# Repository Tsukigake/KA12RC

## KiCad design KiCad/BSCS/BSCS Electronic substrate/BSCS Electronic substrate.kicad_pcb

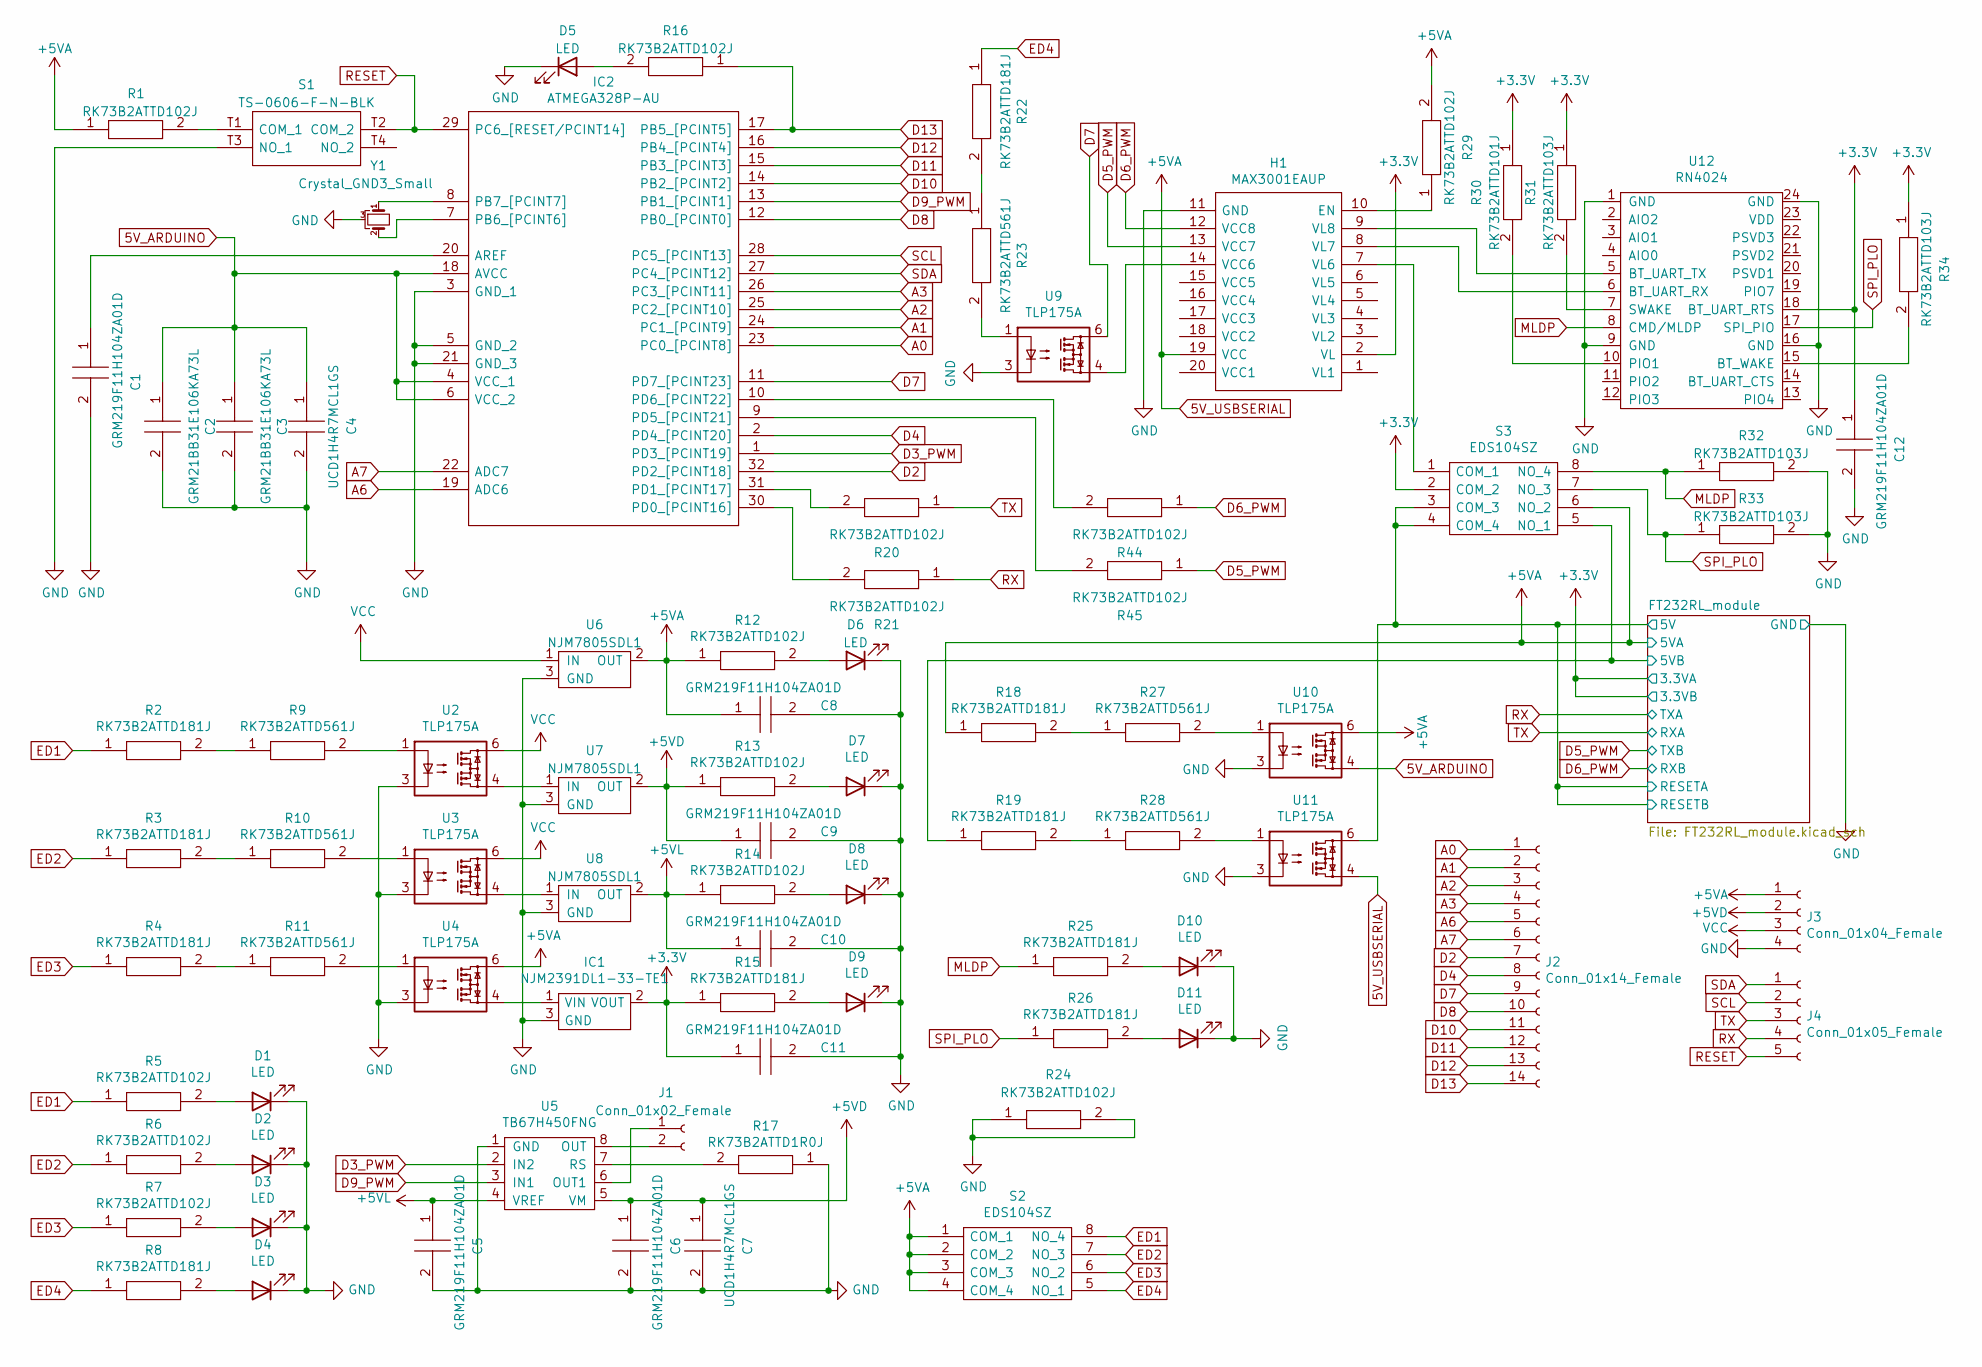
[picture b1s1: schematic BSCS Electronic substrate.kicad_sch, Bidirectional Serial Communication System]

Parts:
C1, C5, C6, C8, C9, C10, C11, C12: GRM219F11H104ZA01D; CAPC2012X95N; Manufacturer_Part_Number GRM219F11H104ZA01D
C2, C3: GRM21BB31E106KA73L; CAPC2012X140N; Manufacturer_Part_Number GRM21BB31E106KA73L
C4, C7: UCD1H4R7MCL1GS; CAPAE430X610N; Manufacturer_Part_Number UCD1H4R7MCL1GS
D1, D2, D3, D4, D5, D6, D7, D8, D9, D10, D11: LED; OSXX0603C1E
H1: MAX3001EAUP; SOP65P640X110-20N; Manufacturer_Part_Number MAX3001EAUP
IC1: NJM2391DL1-33-TE1; TO-252-3-L1; Manufacturer_Part_Number NJM2391DL1-33-TE1
IC2: ATMEGA328P-AU; QFP80P900X900X120-32N; Manufacturer_Part_Number ATMEGA328P-AU
J1: Conn_01x02_Female; PinHeader_1x02_P2.54mm_Vertical
J2: Conn_01x14_Female; PinHeader_1x14_P2.54mm_Vertical
J3: Conn_01x04_Female; PinHeader_1x04_P2.54mm_Vertical
J4: Conn_01x05_Female; PinHeader_1x05_P2.54mm_Vertical
R1, R5, R6, R7, R12, R13, R14, R16, R20, R21, R24, R29, R44, R45: RK73B2ATTD102J; RESC2012X60N; Manufacturer_Part_Number RK73B2ATTD102J
R2, R3, R4, R8, R15, R18, R19, R22, R25, R26: RK73B2ATTD181J; RESC2012X60N; Manufacturer_Part_Number RK73B2ATTD181J
R9, R10, R11, R23, R27, R28: RK73B2ATTD561J; RESC2012X60N; Manufacturer_Part_Number RK73B2ATTD561J
R17: RK73B2ATTD1R0J; RESC2012X60N; Manufacturer_Part_Number RK73B2ATTD1R0J
R30: RK73B2ATTD101J; RESC2012X60N; Manufacturer_Part_Number RK73B2ATTD101J
R31, R32, R33, R34: RK73B2ATTD103J; RESC2012X60N; Manufacturer_Part_Number RK73B2ATTD103J
S1: TS-0606-F-N-BLK; TS0606FNBLK; Manufacturer_Part_Number TS-0606-F-N-BLK
S2, S3: EDS104SZ; KHS42E; Manufacturer_Part_Number EDS104SZ
U2, U3, U4, U9, U10, U11: TLP175A; MFSOP6-4_4.4x3.6mm_P1.27mm
U5: TB67H450FNG; NE555DR
U6, U7, U8: NJM7805SDL1; TO-252-3-L1
U12: RN4024
Y1: Crystal_GND3_Small; CSTCE16M0V53R0

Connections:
5V_ARDUINO: C2.1, C3.1, C4.1, IC2.4 (VCC_1), IC2.6 (VCC_2), IC2.18 (AVCC), U10.4
5V_USBSERIAL: C8.1, H1.19 (VCC), J3.1, R1.1, R12.1, R18.1, R29.2, S2.1 (COM_1), S2.2 (COM_2), S2.3 (COM_3), S2.4 (COM_4), S3.6 (NO_2), U4.6, U6.2 (OUT), U10.6, U11.4; also elsewhere on the board
+3V3: C11.1, C12.1, H1.2 (VL), IC1.2 (VOUT), R15.1, R30.1, R31.1, R34.1, S3.2 (COM_2), U12.18 (BT_UART_RTS); also elsewhere on the board
+5VD: C6.1, C7.1, C9.1, J3.2, R13.1, U5.5 (VM), U7.2 (OUT)
+5VL: C5.1, C10.1, R14.1, U5.4 (VREF), U8.2 (OUT)
/FT232RL_module/5V: S3.3 (COM_3), S3.4 (COM_4), U11.6; also elsewhere on the board
/FT232RL_module/5VB: R19.1, S3.5 (NO_1); also elsewhere on the board
A0: IC2.23 (PC0_[PCINT8]), J2.1
A1: IC2.24 (PC1_[PCINT9]), J2.2
A2: IC2.25 (PC2_[PCINT10]), J2.3
A3: IC2.26 (PC3_[PCINT11]), J2.4
A6: IC2.19 (ADC6), J2.5
A7: IC2.22 (ADC7), J2.6
D2: IC2.32 (PD2_[PCINT18]), J2.7
D3_PWM: IC2.1 (PD3_[PCINT19]), U5.2 (IN2)
D4: IC2.2 (PD4_[PCINT20]), J2.8
D5_PWM: H1.13 (VCC7), R45.1; also elsewhere on the board
D6_PWM: H1.12 (VCC8), R44.1; also elsewhere on the board
D7: IC2.11 (PD7_[PCINT23]), J2.9, U9.6
D8: IC2.12 (PB0_[PCINT0]), J2.10
D9_PWM: IC2.13 (PB1_[PCINT1]), U5.3 (IN1)
D10: IC2.14 (PB2_[PCINT2]), J2.11
D11: IC2.15 (PB3_[PCINT3]), J2.12
D12: IC2.16 (PB4_[PCINT4]), J2.13
D13: IC2.17 (PB5_[PCINT5]), J2.14, R16.1
ED1: R2.1, R5.1, S2.8 (NO_4)
ED2: R3.1, R6.1, S2.7 (NO_3)
ED3: R4.1, R7.1, S2.6 (NO_2)
ED4: R8.1, R22.1, S2.5 (NO_1)
GND: C1.2, C2.2, C3.2, C4.2, C5.2, C6.2, C7.2, C8.2, C9.2, C10.2, C11.2, C12.2, D1.1 (K), D2.1 (K), D3.1 (K), D4.1 (K), D5.1 (K), D6.1 (K), D7.1 (K), D8.1 (K), D9.1 (K), D10.1 (K), D11.1 (K), H1.11 (GND), IC1.3 (GND), IC2.3 (GND_1), IC2.5 (GND_2), IC2.21 (GND_3), J3.4, R17.1, R24.1, R24.2, R32.2, R33.2, S1.T3 (NO_1), U2.3, U3.3, U4.3, U5.1 (GND), U6.3 (GND), U7.3 (GND), U8.3 (GND), U9.3, U10.3, U11.3, U12.1 (GND), U12.9 (GND), U12.16 (GND), U12.24 (GND), Y1.3; also elsewhere on the board
MLDP: R25.1, R32.1, S3.8 (NO_4), U12.8 (CMD/MLDP)
unnamed: C1.1, IC2.20 (AREF)
unnamed: D1.2 (A), R5.2
unnamed: D2.2 (A), R6.2
unnamed: D3.2 (A), R7.2
unnamed: D4.2 (A), R8.2
unnamed: D5.2 (A), R16.2
unnamed: D6.2 (A), R12.2
unnamed: D7.2 (A), R13.2
unnamed: D8.2 (A), R14.2
unnamed: D9.2 (A), R15.2
unnamed: D10.2 (A), R25.2
unnamed: D11.2 (A), R26.2
unnamed: H1.7 (VL6), S3.1 (COM_1)
unnamed: H1.8 (VL7), U12.6 (BT_UART_RX)
unnamed: H1.9 (VL8), U12.5 (BT_UART_TX)
unnamed: H1.10 (EN), R29.1
unnamed: H1.14 (VCC6), U9.4
unnamed: IC1.1 (VIN), U4.4
unnamed: IC2.7 (PB6_[PCINT6]), Y1.2
unnamed: IC2.8 (PB7_[PCINT7]), Y1.1
unnamed: IC2.9 (PD5_[PCINT21]), R45.2
unnamed: IC2.10 (PD6_[PCINT22]), R44.2
unnamed: IC2.30 (PD0_[PCINT16]), R21.2
unnamed: IC2.31 (PD1_[PCINT17]), R20.2
unnamed: J1.1, U5.6 (OUT1)
unnamed: J1.2, U5.8 (OUT)
unnamed: R1.2, S1.T1 (COM_1)
unnamed: R2.2, R9.1
unnamed: R9.2, U2.1
unnamed: R3.2, R10.1
unnamed: R10.2, U3.1
unnamed: R4.2, R11.1
unnamed: R11.2, U4.1
unnamed: R17.2, U5.7 (RS)
unnamed: R18.2, R27.1
unnamed: R19.2, R28.1
unnamed: R22.2, R23.1
unnamed: R23.2, U9.1
unnamed: R27.2, U10.1
unnamed: R28.2, U11.1
unnamed: R30.2, U12.10 (PIO1)
unnamed: R31.2, U12.7 (SWAKE)
unnamed: R34.2, U12.15 (BT_WAKE)
unnamed: U2.4, U7.1 (IN)
unnamed: U3.4, U8.1 (IN)
RESET: IC2.29 (PC6_[RESET/PCINT14]), J4.5, S1.T2 (COM_2)
RX: J4.4, R21.1; also elsewhere on the board
SCL: IC2.28 (PC5_[PCINT13]), J4.2
SDA: IC2.27 (PC4_[PCINT12]), J4.1
SPI_PLO: R26.1, R33.1, S3.7 (NO_3), U12.17 (SPI_PIO)
TX: J4.3, R20.1; also elsewhere on the board
VCC: J3.3, U2.6, U3.6, U6.1 (IN)

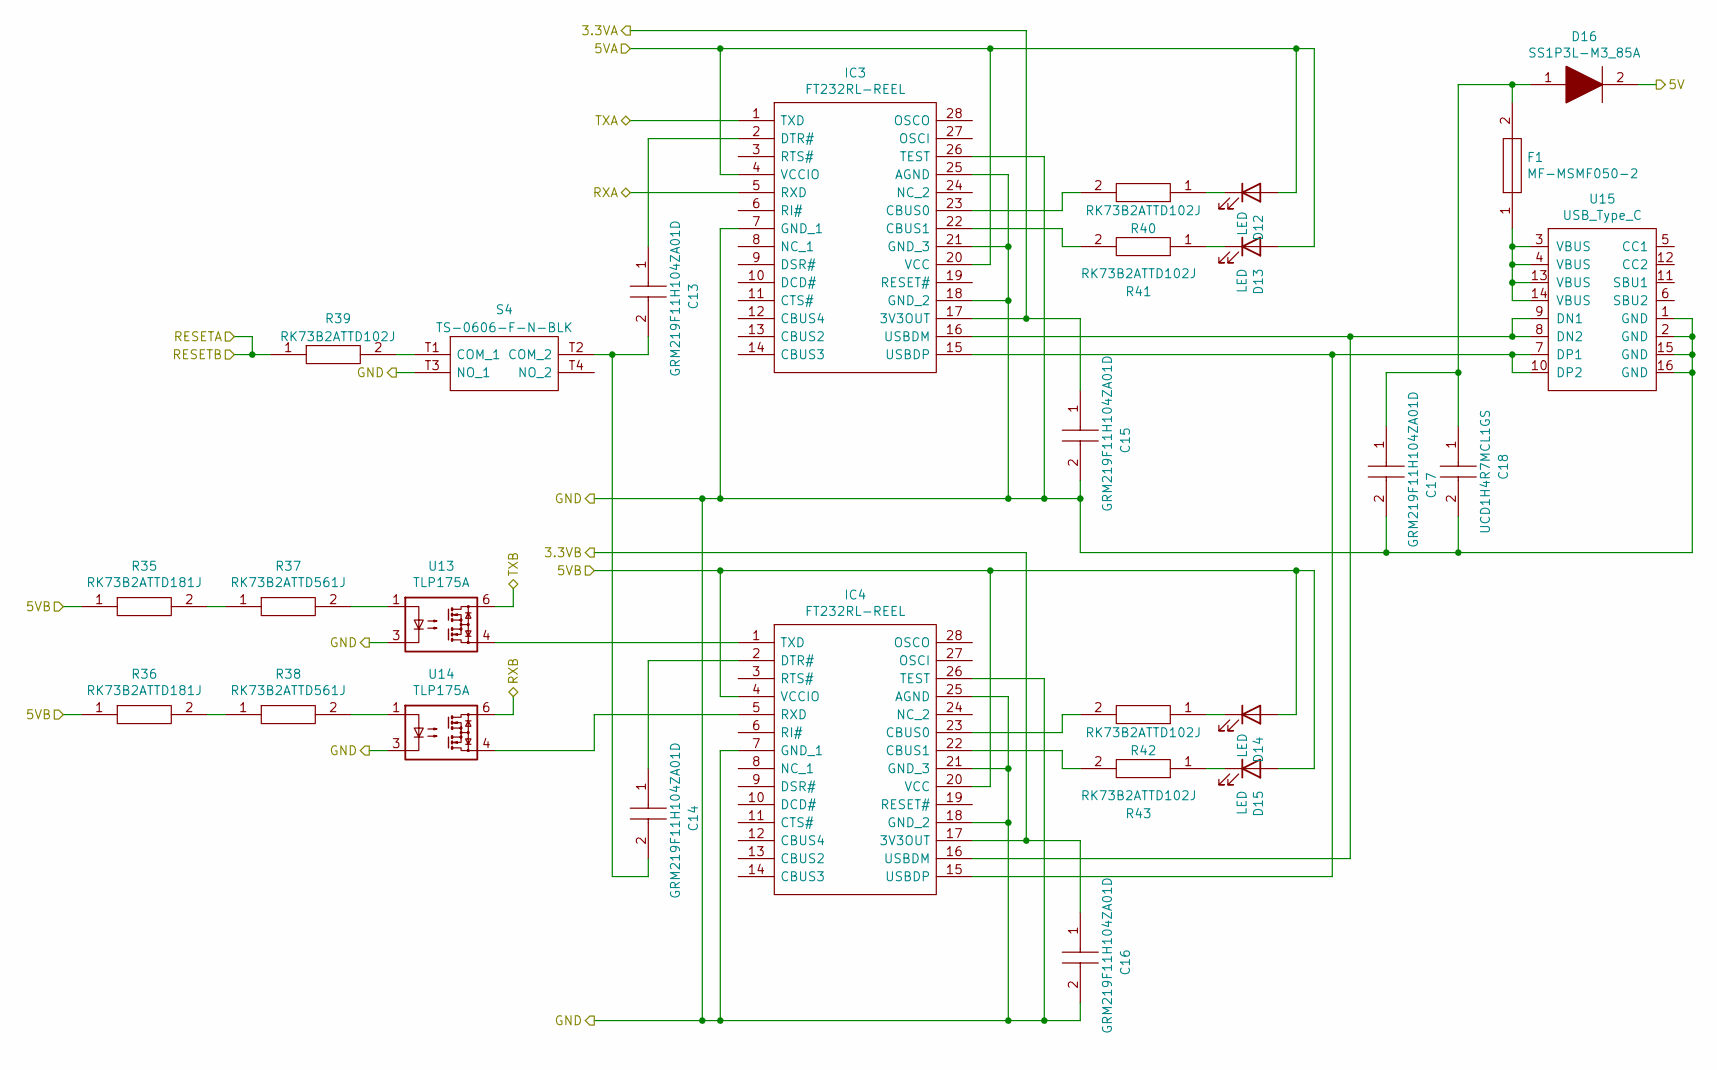
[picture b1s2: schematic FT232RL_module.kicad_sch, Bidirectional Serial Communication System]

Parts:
C13, C14, C15, C16, C17: GRM219F11H104ZA01D; CAPC2012X95N; Manufacturer_Part_Number GRM219F11H104ZA01D
C18: UCD1H4R7MCL1GS; CAPAE430X610N; Manufacturer_Part_Number UCD1H4R7MCL1GS
D12, D13, D14, D15: LED; OSXX0603C1E
D16: SS1P3L-M3_85A; SMP; Manufacturer_Part_Number SS1P3L-M3/85A
F1: MF-MSMF050-2; FUSC4632X85N; Manufacturer_Part_Number MF-MSMF050-2
IC3, IC4: FT232RL-REEL; SOP65P778X200-28N; Manufacturer_Part_Number FT232RL-REEL
R35, R36: RK73B2ATTD181J; RESC2012X60N; Manufacturer_Part_Number RK73B2ATTD181J
R37, R38: RK73B2ATTD561J; RESC2012X60N; Manufacturer_Part_Number RK73B2ATTD561J
R39, R40, R41, R42, R43: RK73B2ATTD102J; RESC2012X60N; Manufacturer_Part_Number RK73B2ATTD102J
S4: TS-0606-F-N-BLK; TS0606FNBLK; Manufacturer_Part_Number TS-0606-F-N-BLK
U13, U14: TLP175A; MFSOP6-4_4.4x3.6mm_P1.27mm
U15: USB_Type_C

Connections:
5V_USBSERIAL: D12.2 (A), D13.2 (A), IC3.4 (VCCIO), IC3.20 (VCC); also elsewhere on the board
+3V3: C15.1, C16.1, IC3.17 (3V3OUT), IC4.17 (3V3OUT); also elsewhere on the board
/FT232RL_module/5V: D16.2, R39.1; also elsewhere on the board
/FT232RL_module/5VB: D14.2 (A), D15.2 (A), IC4.4 (VCCIO), IC4.20 (VCC), R35.1, R36.1; also elsewhere on the board
D5_PWM: U13.6; also elsewhere on the board
D6_PWM: U14.6; also elsewhere on the board
GND: C15.2, C16.2, C17.2, C18.2, IC3.7 (GND_1), IC3.18 (GND_2), IC3.21 (GND_3), IC3.25 (AGND), IC3.26 (TEST), IC4.7 (GND_1), IC4.18 (GND_2), IC4.21 (GND_3), IC4.25 (AGND), IC4.26 (TEST), S4.T3 (NO_1), U13.3, U14.3, U15.1 (GND), U15.2 (GND), U15.15 (GND), U15.16 (GND); also elsewhere on the board
unnamed: C13.1, IC3.2 (DTR#)
unnamed: C13.2, C14.2, S4.T2 (COM_2)
unnamed: C14.1, IC4.2 (DTR#)
unnamed: C17.1, C18.1, D16.1, F1.2
unnamed: D12.1 (K), R40.1
unnamed: D13.1 (K), R41.1
unnamed: D14.1 (K), R42.1
unnamed: D15.1 (K), R43.1
unnamed: F1.1, U15.3 (VBUS), U15.4 (VBUS), U15.13 (VBUS), U15.14 (VBUS)
unnamed: IC3.15 (USBDP), IC4.15 (USBDP), U15.7 (DP1), U15.10 (DP2)
unnamed: IC3.16 (USBDM), IC4.16 (USBDM), U15.8 (DN2), U15.9 (DN1)
unnamed: IC3.22 (CBUS1), R41.2
unnamed: IC3.23 (CBUS0), R40.2
unnamed: IC4.1 (TXD), U13.4
unnamed: IC4.5 (RXD), U14.4
unnamed: IC4.22 (CBUS1), R43.2
unnamed: IC4.23 (CBUS0), R42.2
unnamed: R35.2, R37.1
unnamed: R36.2, R38.1
unnamed: R37.2, U13.1
unnamed: R38.2, U14.1
unnamed: R39.2, S4.T1 (COM_1)
RX: IC3.1 (TXD); also elsewhere on the board
TX: IC3.5 (RXD); also elsewhere on the board

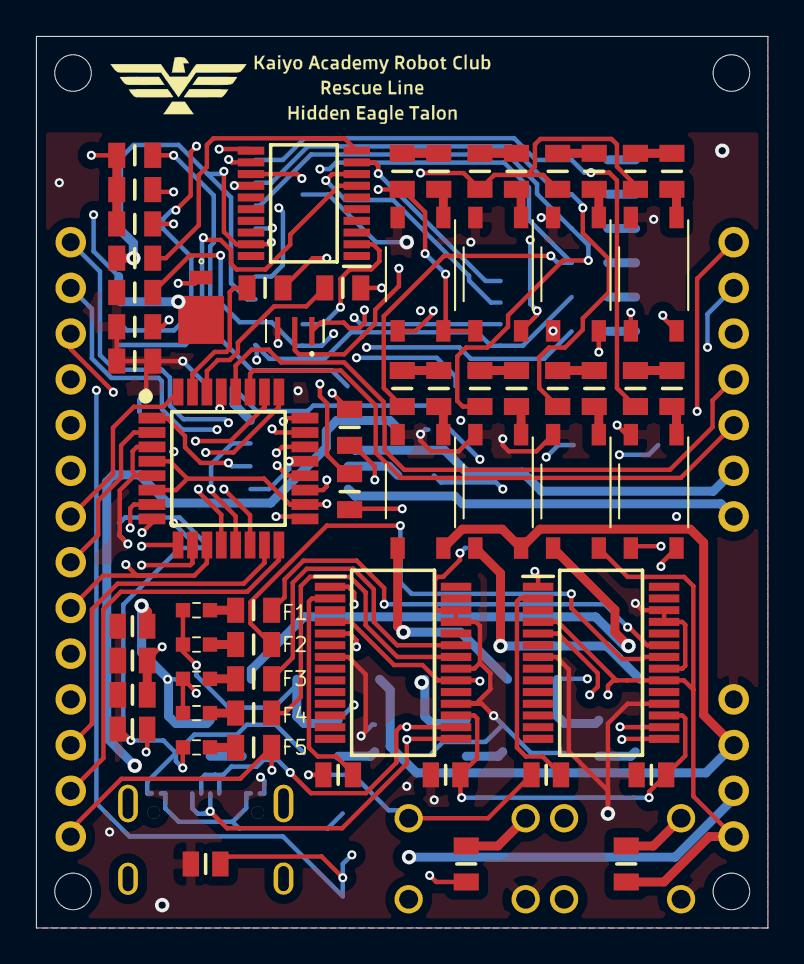
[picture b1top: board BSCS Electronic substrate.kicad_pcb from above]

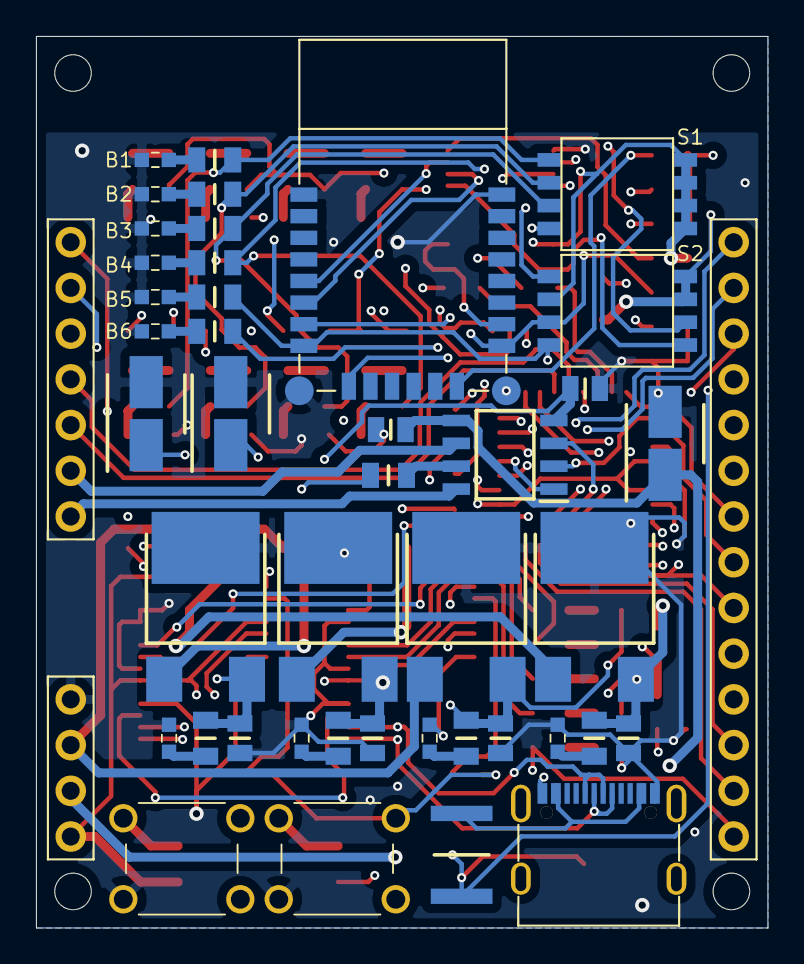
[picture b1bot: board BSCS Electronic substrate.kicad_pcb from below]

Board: 4 copper layers, 40.6 x 49.5 mm, 108 parts (46 on the bottom side), 105 nets.

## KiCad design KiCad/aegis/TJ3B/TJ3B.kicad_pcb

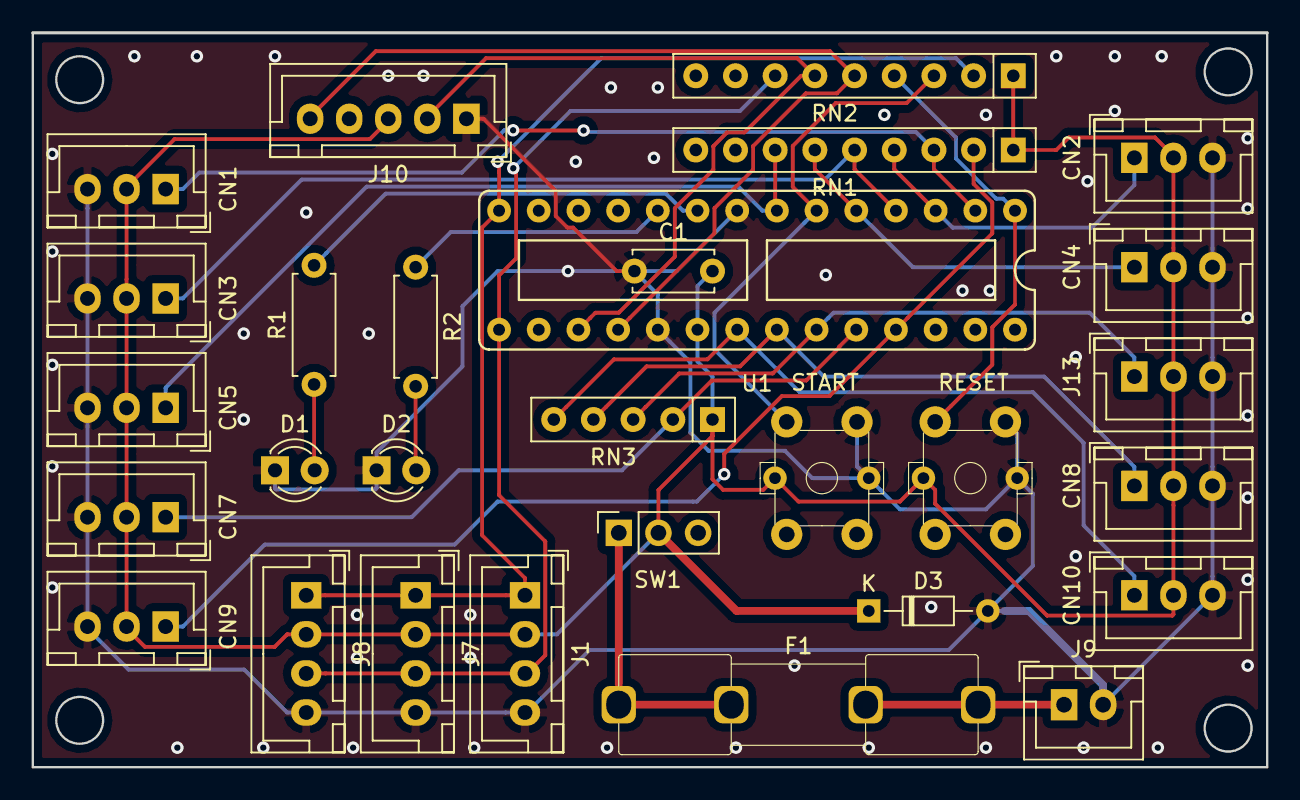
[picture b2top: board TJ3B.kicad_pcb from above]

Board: 2 copper layers, 79.0 x 47.0 mm, 29 parts (0 on the bottom side), 24 nets.

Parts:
C1: 0.1u; C_Disc_D5.0mm_W2.5mm_P5.00mm
CN1, CN2, CN3, CN4, CN5, CN7, CN8, CN9, CN10: Conn_01x03_Female; JST_XH_B03B-XH-A_1x03_P2.50mm_Vertical
D1, D2: LED; LED_D3.0mm
D3: D; D_DO-34_SOD68_P7.62mm_Horizontal
F1: Fuse; fuse
J1, J7, J8: Conn_01x04_Female; JST_XH_B04B-XH-A_1x04_P2.50mm_Vertical
J9: Conn_01x02_Female; JST_XH_B02B-XH-A_1x02_P2.50mm_Vertical
J10: Conn_01x05_Female; JST_XH_B05B-XH-A_1x05_P2.50mm_Vertical
J13: Conn_01x03_Female; JST_XH_B03B-XH-A_1x03_P2.50mm_Vertical
R1, R2: 330; R_Axial_DIN0207_L6.3mm_D2.5mm_P7.62mm_Horizontal
RESET: LS601-CU
RN1: R_100k; R_Array_SIP9
RN2: R_10k; R_Array_SIP9
RN3: R_100k; R_Array_SIP5
START: LS601-CU
SW1: SW_DIP_x01; PinSocket_1x03_P2.54mm_Vertical
U1: PIC18F2620; 2227-28-03

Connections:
+5V: C1.2, CN1.2, CN2.2, CN3.2, CN4.2, CN5.2, CN7.2, CN8.2, CN9.2, CN10.2, D3.1, J1.2, J7.2, J8.2, J10.3, J13.2, RESET.5, RN1.1, RN2.1, RN3.1, START.5, SW1.2, U1.20
AD1: CN1.1, RN1.3, U1.2
AD2: CN2.1, RN1.4, U1.3
AD3: CN3.1, RN1.5, U1.4
AD4: CN4.1, RN1.6, U1.5
AD5: CN5.1, RN1.7, U1.7
AD6: J13.1, RN3.3, U1.23
AD7: CN7.1, RN3.2, U1.24
AD8: CN8.1, RN3.4, U1.22
AD9: CN9.1, RN1.2, U1.25
AD10: CN10.1, RN3.5, U1.21
GND: C1.1, CN1.3, CN2.3, CN3.3, CN4.3, CN5.3, CN7.3, CN8.3, CN9.3, CN10.3, D1.1, D2.1, D3.2, J1.4, J7.4, J8.4, J9.2, J10.1, J13.3, RESET.1, RESET.6, START.1, START.6, U1.8, U1.19
MCLR: RESET.3, RN2.4, U1.1
MON_LED: R2.1, U1.10
unnamed: D1.2, R1.1
unnamed: D2.2, R2.2
unnamed: F1.1, SW1.1
unnamed: F1.2, J9.1
PWM_LED: R1.2, U1.9
RA4: RN2.3, START.3, U1.6
RX: J10.5, RN2.5, U1.18
SCL: J1.1, J7.1, J8.1, RN2.2, U1.14
SDA: J1.3, J7.3, J8.3, RN2.7, U1.15
TX: J10.2, RN2.6, U1.17

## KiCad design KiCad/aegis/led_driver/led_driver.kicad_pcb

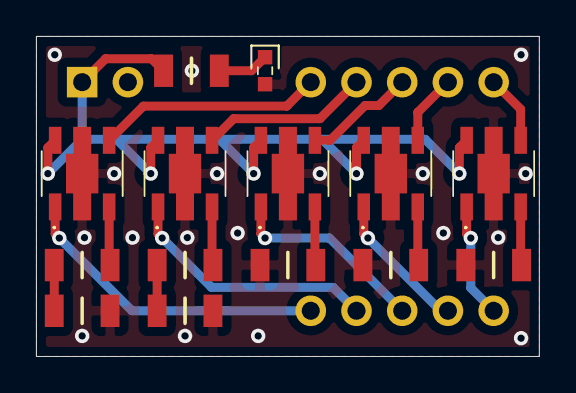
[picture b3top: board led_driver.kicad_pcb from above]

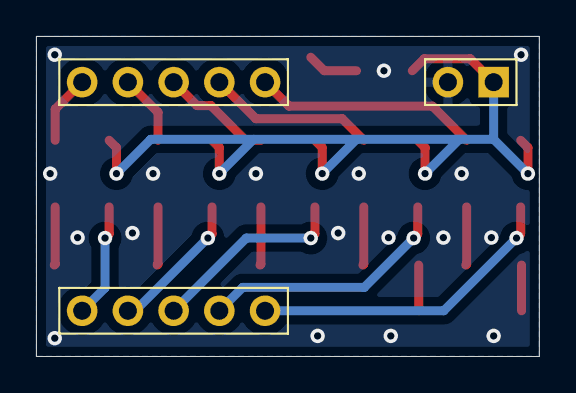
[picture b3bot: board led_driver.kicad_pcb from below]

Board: 2 copper layers, 27.9 x 17.8 mm, 17 parts (3 on the bottom side), 20 nets.

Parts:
J1: Conn_01x02_Male; PinHeader_1x02_P2.54mm_Vertical
J2, J3: Conn_01x05_Male; PinHeader_1x05_P2.54mm_Vertical
J5, J6, J7, J10, J11: NJW4616U2
LED1: OSXX0603C1E
R1, R2, R3, R4, R5, R6, R7: RK73B2BTTD1R0J; RESC3216X80N
R8: RK73B2BTTD221J; RESC3216X70N

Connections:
unnamed: J1.1, J5.6, J6.6, J7.6, J10.6, J11.6, R8.1
unnamed: J1.2, J5.2, J5.5, J5.7, J6.2, J6.5, J6.7, J7.2, J7.5, J7.7, J10.2, J10.5, J10.7, J11.2, J11.5, J11.7, LED1.2, R1.2, R2.2, R3.2, R6.2, R7.2
unnamed: J2.1, J5.1
unnamed: J2.2, J6.1
unnamed: J2.3, J7.1
unnamed: J3.1, J5.4
unnamed: J3.2, J6.4
unnamed: J3.3, J7.4
unnamed: J5.3, R1.1
unnamed: J6.3, R2.1
unnamed: J7.3, R3.1
unnamed: J2.4, J10.1
unnamed: J10.3, R4.1
unnamed: J3.4, J10.4
unnamed: J2.5, J11.1
unnamed: J11.3, R5.1
unnamed: J3.5, J11.4
unnamed: LED1.1, R8.2
unnamed: R4.2, R6.1
unnamed: R5.2, R7.1

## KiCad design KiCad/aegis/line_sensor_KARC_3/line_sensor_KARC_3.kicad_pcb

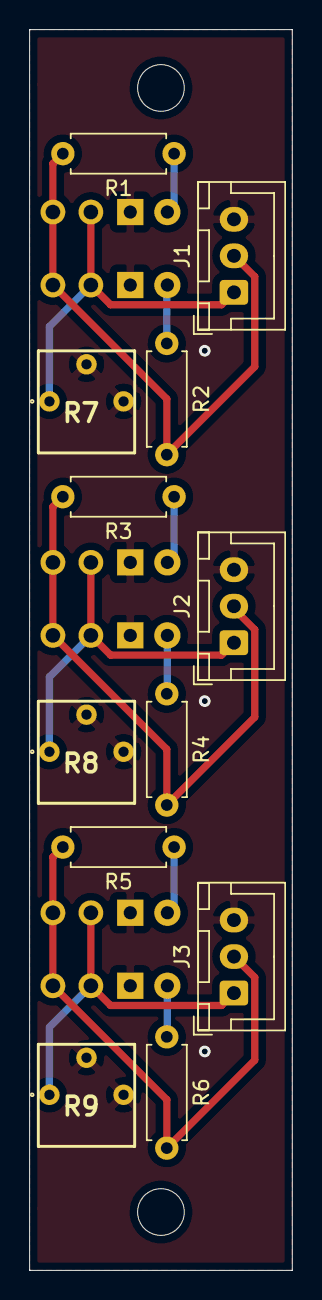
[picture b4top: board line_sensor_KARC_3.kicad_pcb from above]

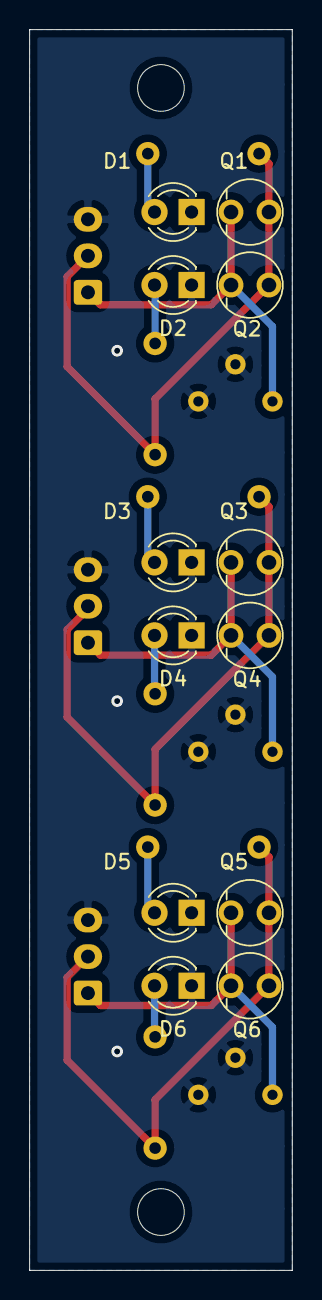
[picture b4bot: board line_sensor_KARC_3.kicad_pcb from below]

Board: 2 copper layers, 18.0 x 85.0 mm, 24 parts (12 on the bottom side), 13 nets.

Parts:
D1, D2, D3, D4, D5, D6: LED; LED_D3.0mm_Clear
J1, J2, J3: Conn_01x03_Male; JST_XH_B3B-XH-A_1x03_P2.50mm_Vertical
Q1, Q2, Q3, Q4, Q5, Q6: Q_Photo_NPN; NJL7502L
R1, R2, R3, R4, R5, R6: R; R_Axial_DIN0207_L6.3mm_D2.5mm_P7.62mm_Horizontal
R7, R8, R9: 3362P-1-203LF; 3362P_1

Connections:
unnamed: D1.1, D2.1, D3.1, D4.1, D5.1, D6.1, J1.3, J2.3, J3.3, R7.2, R7.3, R8.2, R8.3, R9.2, R9.3
unnamed: D1.2, R1.1
unnamed: D2.2, R2.1
unnamed: D3.2, R3.1
unnamed: D4.2, R4.1
unnamed: D5.2, R5.1
unnamed: D6.2, R6.1
unnamed: J1.1, Q1.2, Q2.2, R7.1
unnamed: J1.2, Q1.1, Q2.1, R1.2, R2.2
unnamed: J2.1, Q3.2, Q4.2, R8.1
unnamed: J2.2, Q3.1, Q4.1, R3.2, R4.2
unnamed: J3.1, Q5.2, Q6.2, R9.1
unnamed: J3.2, Q5.1, Q6.1, R5.2, R6.2

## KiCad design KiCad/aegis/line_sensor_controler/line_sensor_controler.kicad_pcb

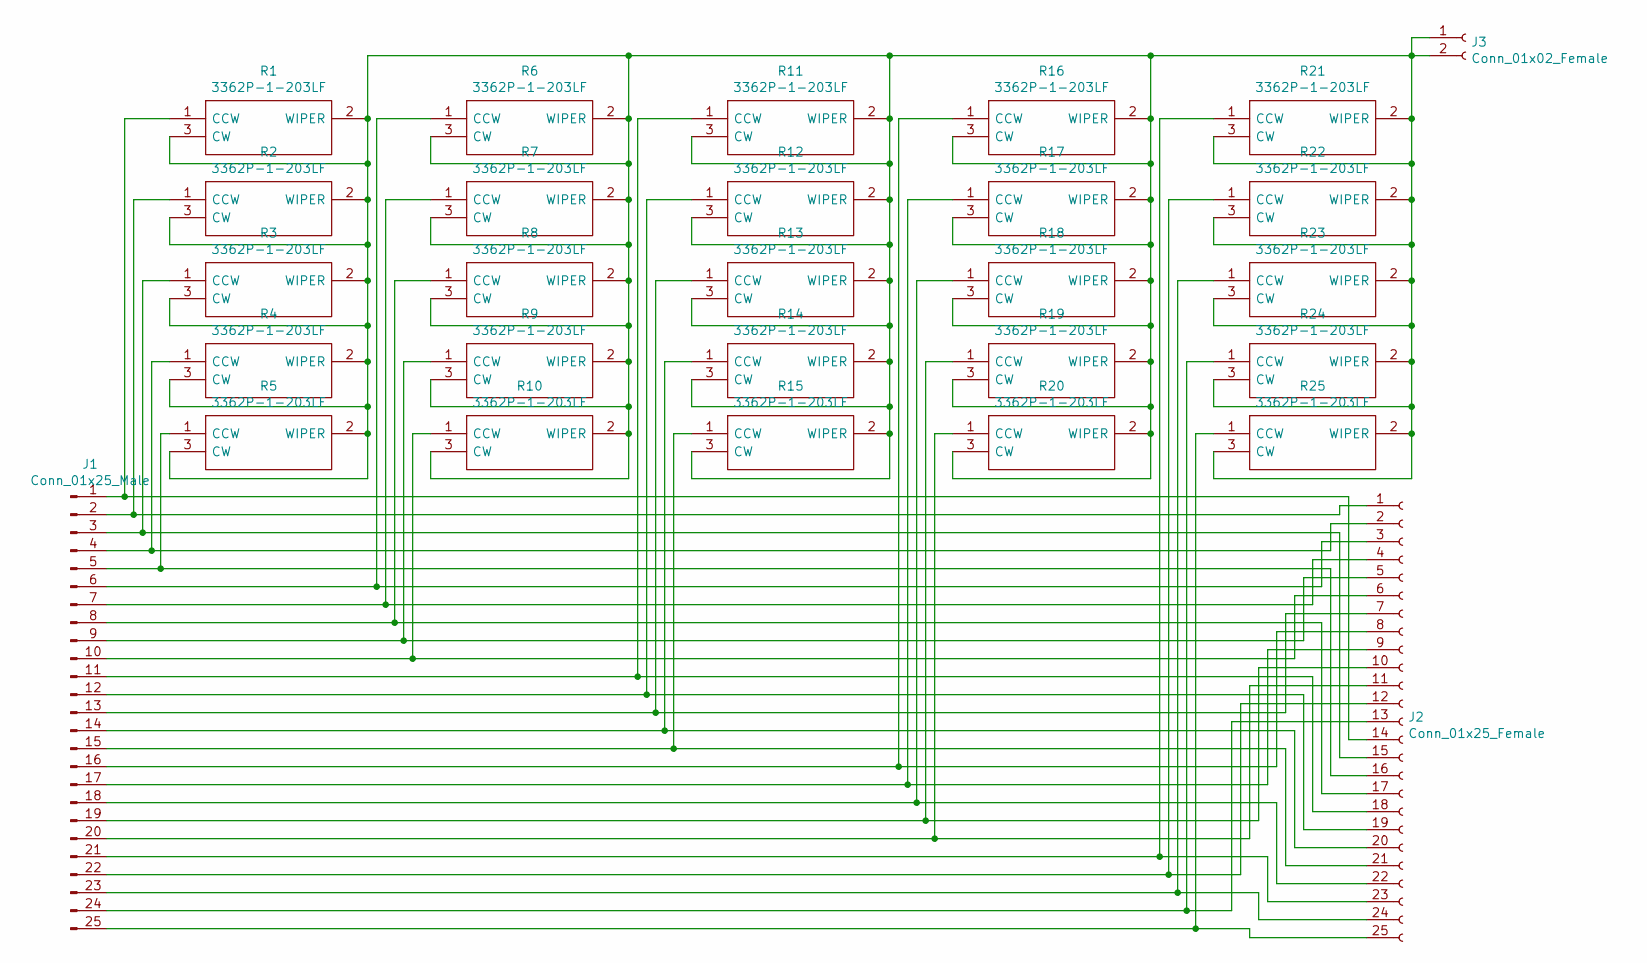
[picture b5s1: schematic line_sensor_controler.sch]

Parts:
J1: Conn_01x25_Male; PinSocket_1x25_P2.54mm_Vertical
J2: Conn_01x25_Female; PinSocket_1x25_P2.54mm_Vertical
J3: Conn_01x02_Female; PinSocket_1x02_P2.54mm_Vertical
R1, R2, R3, R4, R5, R6, R7, R8, R9, R10, R11, R12, R13, R14, R15, R16, R17, R18, R19, R20, R21, R22, R23, R24, R25: 3362P-1-203LF; 3362P_1; Mouser Part Number 652-3362P-1-203LF

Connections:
unnamed: J1.1, J2.14, R1.1 (CCW)
unnamed: J1.2, J2.1, R2.1 (CCW)
unnamed: J1.3, J2.15, R3.1 (CCW)
unnamed: J1.4, J2.2, R4.1 (CCW)
unnamed: J1.5, J2.16, R5.1 (CCW)
unnamed: J1.6, J2.3, R6.1 (CCW)
unnamed: J1.7, J2.4, R7.1 (CCW)
unnamed: J1.8, J2.17, R8.1 (CCW)
unnamed: J1.9, J2.5, R9.1 (CCW)
unnamed: J1.10, J2.6, R10.1 (CCW)
unnamed: J1.11, J2.18, R11.1 (CCW)
unnamed: J1.12, J2.19, R12.1 (CCW)
unnamed: J1.13, J2.7, R13.1 (CCW)
unnamed: J1.14, J2.20, R14.1 (CCW)
unnamed: J1.15, J2.21, R15.1 (CCW)
unnamed: J1.16, J2.8, R16.1 (CCW)
unnamed: J1.17, J2.9, R17.1 (CCW)
unnamed: J1.18, J2.22, R18.1 (CCW)
unnamed: J1.19, J2.10, R19.1 (CCW)
unnamed: J1.20, J2.11, R20.1 (CCW)
unnamed: J1.21, J2.23, R21.1 (CCW)
unnamed: J1.22, J2.12, R22.1 (CCW)
unnamed: J1.23, J2.24, R23.1 (CCW)
unnamed: J1.24, J2.13, R24.1 (CCW)
unnamed: J1.25, J2.25, R25.1 (CCW)
unnamed: J3.1, J3.2, R1.2 (WIPER), R1.3 (CW), R2.2 (WIPER), R2.3 (CW), R3.2 (WIPER), R3.3 (CW), R4.2 (WIPER), R4.3 (CW), R5.2 (WIPER), R5.3 (CW), R6.2 (WIPER), R6.3 (CW), R7.2 (WIPER), R7.3 (CW), R8.2 (WIPER), R8.3 (CW), R9.2 (WIPER), R9.3 (CW), R10.2 (WIPER), R10.3 (CW), R11.2 (WIPER), R11.3 (CW), R12.2 (WIPER), R12.3 (CW), R13.2 (WIPER), R13.3 (CW), R14.2 (WIPER), R14.3 (CW), R15.2 (WIPER), R15.3 (CW), R16.2 (WIPER), R16.3 (CW), R17.2 (WIPER), R17.3 (CW), R18.2 (WIPER), R18.3 (CW), R19.2 (WIPER), R19.3 (CW), R20.2 (WIPER), R20.3 (CW), R21.2 (WIPER), R21.3 (CW), R22.2 (WIPER), R22.3 (CW), R23.2 (WIPER), R23.3 (CW), R24.2 (WIPER), R24.3 (CW), R25.2 (WIPER), R25.3 (CW)

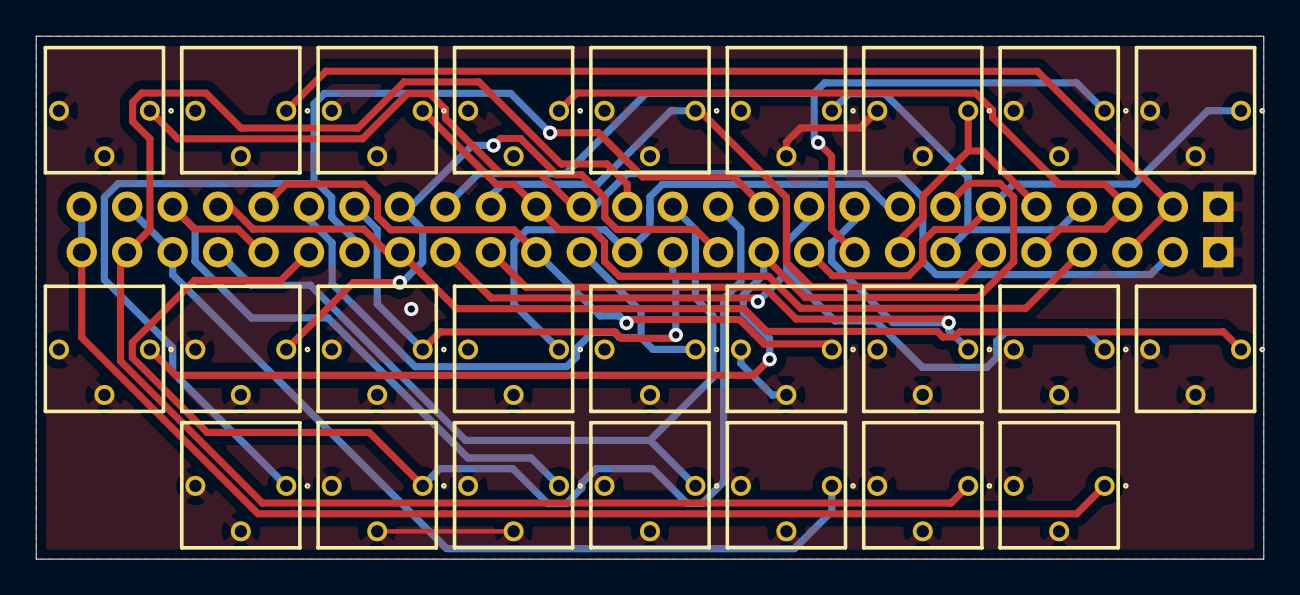
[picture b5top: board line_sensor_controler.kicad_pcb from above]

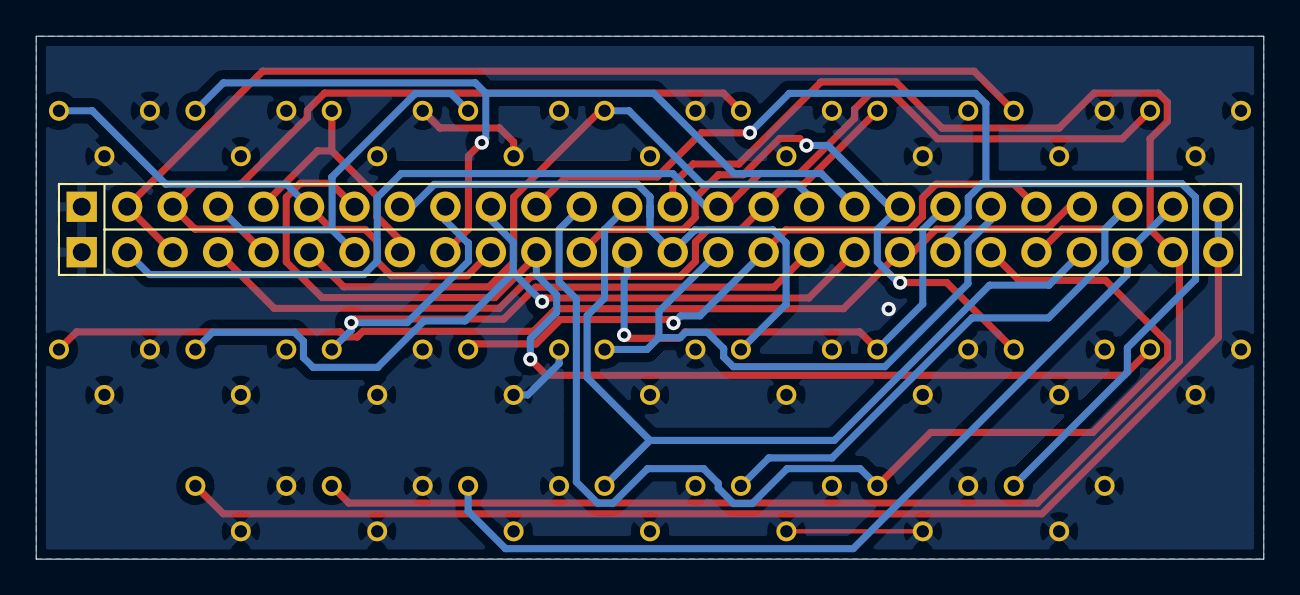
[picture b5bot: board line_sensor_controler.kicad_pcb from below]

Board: 2 copper layers, 68.6 x 29.2 mm, 28 parts (3 on the bottom side), 26 nets.

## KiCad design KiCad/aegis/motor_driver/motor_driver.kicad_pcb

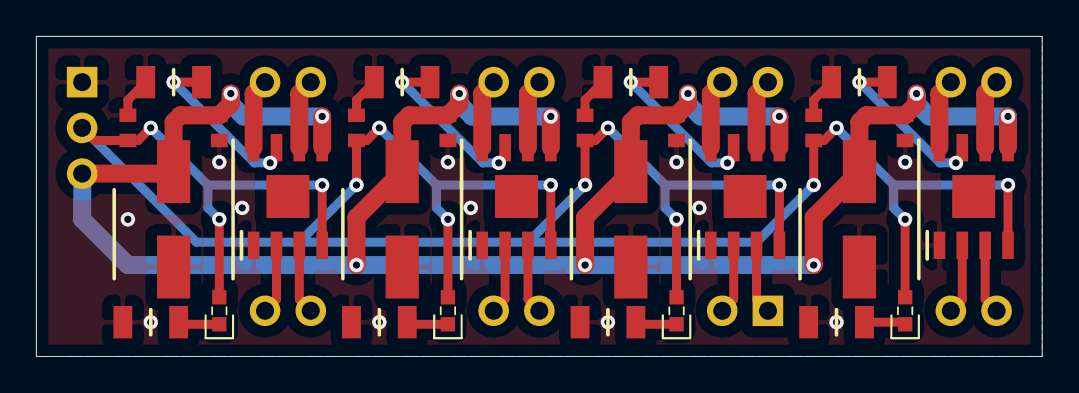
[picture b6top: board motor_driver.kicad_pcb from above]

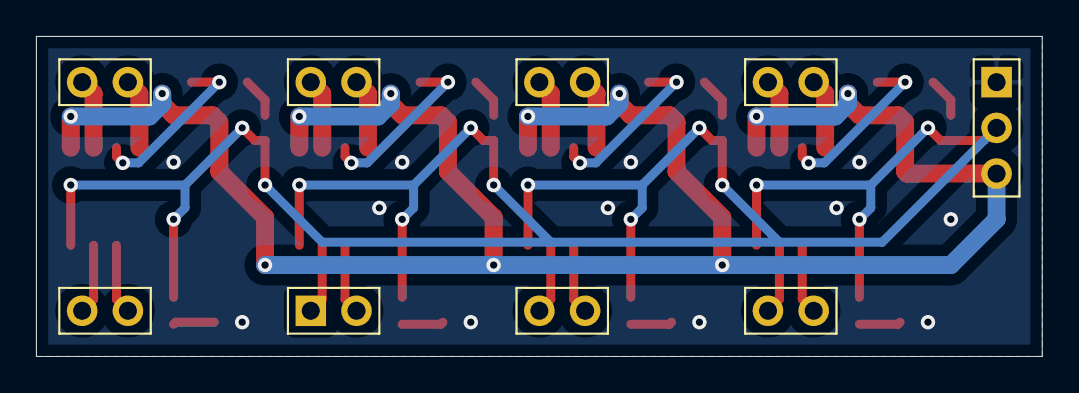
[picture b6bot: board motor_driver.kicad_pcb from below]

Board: 2 copper layers, 55.9 x 17.8 mm, 37 parts (9 on the bottom side), 27 nets.

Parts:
C1, C2, C3, C4, C5, C6, C7, C8: 0.1u; CAPC1608X90N
C9, C10, C11, C12: 47u; CAPAE660X730N
D1, D2, D3, D4: LED; OSXX0603C1E
J1: Conn_01x03_Female; PinHeader_1x03_P2.54mm_Vertical
J2, J3, J4, J5, J6, J7, J8, J9: Conn_01x02_Female; PinHeader_1x02_P2.54mm_Vertical
R1, R2, R3, R4: 110; RESC3216X70N
R5, R6, R7, R8: 1; RESC3216X80N
U3, U4, U5, U6: TB67H450FNG; SOIC127P600X175-9N

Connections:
unnamed: C1.1, C2.1, C3.1, C4.1, D1.2, D2.2, D3.2, D4.2, J1.2, U3.4, U4.4, U5.4, U6.4
unnamed: C1.2, C2.2, C3.2, C4.2, C5.2, C6.2, C7.2, C8.2, C9.2, C10.2, C11.2, C12.2, J1.1, R1.1, R2.1, R3.1, R4.1, R5.1, R6.1, R7.1, R8.1, U3.1, U4.1, U5.1, U6.1
unnamed: C5.1, C6.1, C7.1, C8.1, C9.1, C10.1, C11.1, C12.1, J1.3, U3.5, U4.5, U5.5, U6.5
unnamed: D1.1, R1.2
unnamed: D2.1, R2.2
unnamed: D3.1, R3.2
unnamed: D4.1, R4.2
unnamed: J2.1, U3.3
unnamed: J2.2, U3.2
unnamed: J3.1, U4.3
unnamed: J3.2, U4.2
unnamed: J4.1, U5.3
unnamed: J4.2, U5.2
unnamed: J5.1, U6.3
unnamed: J5.2, U6.2
unnamed: J6.1, U3.8
unnamed: J6.2, U3.6
unnamed: J7.1, U4.8
unnamed: J7.2, U4.6
unnamed: J8.1, U5.8
unnamed: J8.2, U5.6
unnamed: J9.1, U6.8
unnamed: J9.2, U6.6
unnamed: R5.2, U3.7
unnamed: R6.2, U4.7
unnamed: R7.2, U5.7
unnamed: R8.2, U6.7
